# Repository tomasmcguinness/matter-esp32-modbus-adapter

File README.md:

# Matter ESP32 Modbus Adapter
The goal of this project is to provide a simple working Modbus adapter. It is designed for the ESP32-C6 MCU, so can be used with ESPHome, ESP-IDF and Arduino.

> [!WARNING]
> This is a work in progress. The code is working without issue, but the PCB (Revision A) has some design issues, which need addressing.

# Hardware

The hardware folder contains a KiCad PCB design, designed around the ESP32-C6-MINI-1. Both the antenna and non-antenna versions will work here.

# SDM120M - Electrical Sensor

The first device supported by this project is the Eastron SDM120M Single Phase Energy Meter

The readings from this device will be exposed using as a Matter Electrical Sensor Device Type.

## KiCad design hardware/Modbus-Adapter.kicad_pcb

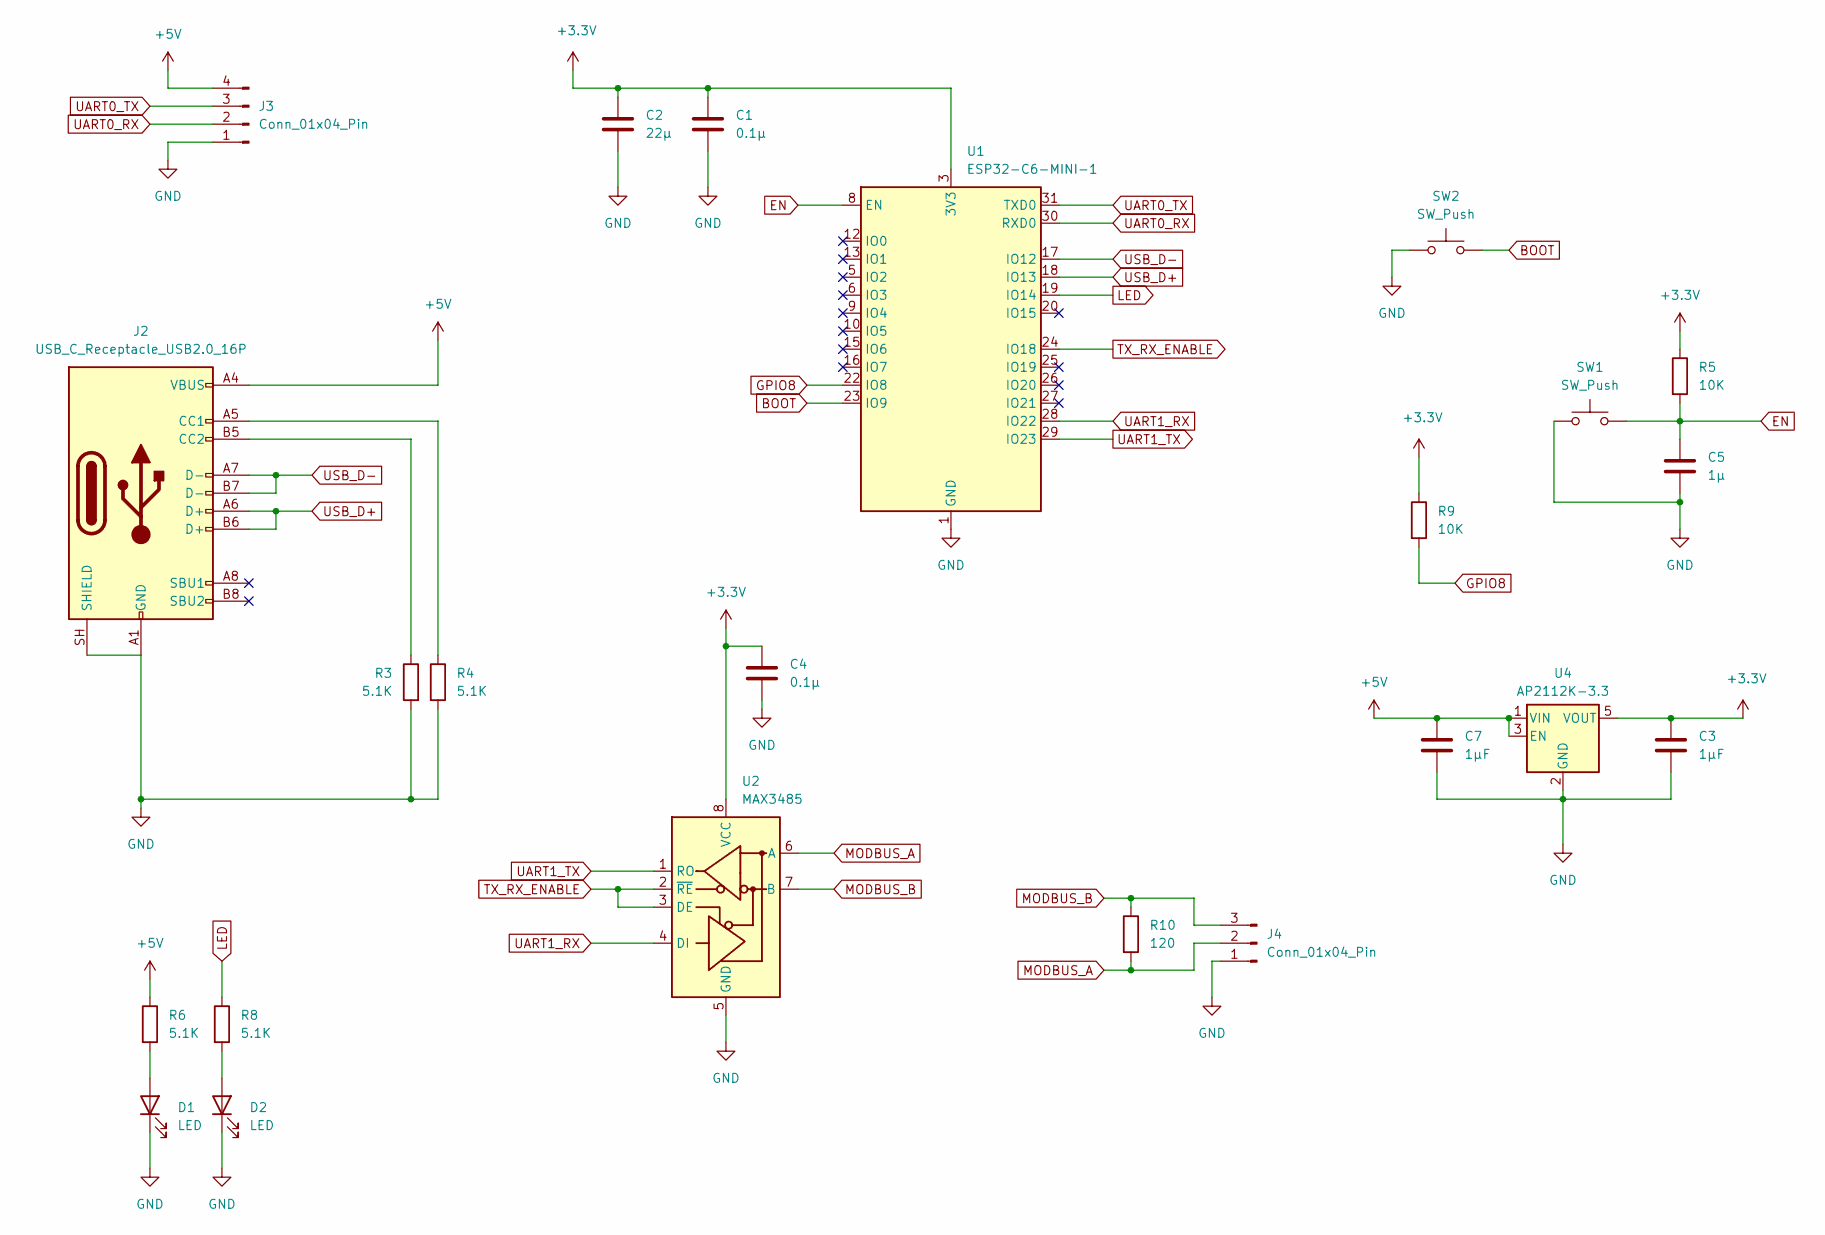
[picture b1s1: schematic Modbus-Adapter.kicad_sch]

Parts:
C1, C4: 0.1µ; C_0805_2012Metric
C2: 22µ; C_0805_2012Metric
C3, C7: 1µF; C_0805_2012Metric
C5: 1µ; C_0805_2012Metric
D1, D2: LED; LED_0805_2012Metric
J2: USB_C_Receptacle_USB2.0_16P; USB_C_Receptacle_GCT_USB4105-xx-A_16P_TopMnt_Horizontal
J3: Conn_01x04_Pin; PinHeader_1x04_P2.54mm_Vertical
J4: Conn_01x04_Pin; TerminalBlock_MaiXu_MX126-5.0-03P_1x03_P5.00mm
R3, R4, R6, R8: 5.1K; R_0805_2012Metric
R5, R9: 10K; R_0805_2012Metric
R10: 120; R_0805_2012Metric
SW1, SW2: SW_Push; SW_SPST_TS-1088-xR025
U1: ESP32-C6-MINI-1
U2: MAX3485; SOIC-8_3.9x4.9mm_P1.27mm
U4: AP2112K-3.3; SOT-23-5

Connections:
+3.3V: C1.1, C2.1, C3.1, C4.1, R5.1, R9.1, U1.3 (3V3), U2.8 (VCC), U4.5 (VOUT)
+5V: C7.1, J2.A4 (VBUS), J2.A9 (VBUS), J2.B4 (VBUS), J2.B9 (VBUS), J3.4, R6.1, U4.1 (VIN), U4.3 (EN)
BOOT: SW2.2, U1.23 (IO9)
EN: C5.1, R5.2, SW1.2, U1.8 (EN)
GND: C1.2, C2.2, C3.2, C4.2, C5.2, C7.2, D1.1 (K), D2.1 (K), J2.A1 (GND), J2.A12 (GND), J2.B1 (GND), J2.B12 (GND), J2.SH (SHIELD), J3.1, J4.1, R3.2, R4.2, SW1.1, SW2.1, U1.1 (GND), U1.2 (GND), U1.11 (GND), U1.14 (GND), U1.36 (GND), U1.37 (GND), U1.38 (GND), U1.39 (GND), U1.40 (GND), U1.41 (GND), U1.42 (GND), U1.43 (GND), U1.44 (GND), U1.45 (GND), U1.46 (GND), U1.47 (GND), U1.48 (GND), U1.49 (GND), U1.50 (GND), U1.51 (GND), U1.52 (GND), U1.53 (GND), U2.5 (GND), U4.2 (GND)
GPIO8: R9.2, U1.22 (IO8)
LED: R8.1, U1.19 (IO14)
MODBUS_A: J4.2, R10.2, U2.6 (A)
MODBUS_B: J4.3, R10.1, U2.7 (B)
unnamed: D1.2 (A), R6.2
unnamed: D2.2 (A), R8.2
unnamed: J2.A5 (CC1), R4.1
unnamed: J2.B5 (CC2), R3.1
TX_RX_ENABLE: U1.24 (IO18), U2.2 (~RE), U2.3 (DE)
UART0_RX: J3.2, U1.30 (RXD0)
UART0_TX: J3.3, U1.31 (TXD0)
UART1_RX: U1.28 (IO22), U2.4 (DI)
UART1_TX: U1.29 (IO23), U2.1 (RO)
USB_D+: J2.A6 (D+), J2.B6 (D+), U1.18 (IO13)
USB_D-: J2.A7 (D-), J2.B7 (D-), U1.17 (IO12)

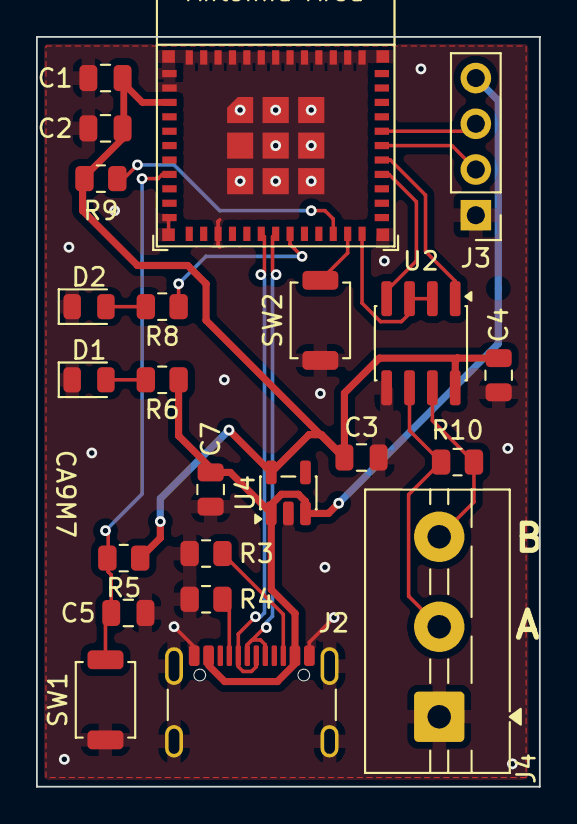
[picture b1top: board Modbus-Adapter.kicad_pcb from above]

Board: 2 copper layers, 27.9 x 41.7 mm, 23 parts (0 on the bottom side), 20 nets.
